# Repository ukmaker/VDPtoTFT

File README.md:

# VDPtoTFT
Converts the output from an old TMS9928A Video Display Processor to drive a small TFT panel using either an SPI or a parallel interface. For lovers of microcomputers from the 70s and 80s.

# Introduction
Once upon a time, when I were a lad, I had my very own Z80 based computer (Nascom 2) which I had built from a kit and then extended with cards of my own design. I always wanted a colour graphics card, and was most envious of computers which used the Texas Instruments TMS9918 family of chips. I never did get a graphics card, though I did build a two-channel DtoA converter and used that to drive my oscilloscope.

So, wind forward to todayish and I'm in the middle of a project to build a drum machine, when I discover a simple computer I'd cobbled together on a breadboard and which was now living in a box in the shed. Putting two and two together, I decided to see whether it would have been possible to build the drum machine using 70s technology. First thing to do was to decide on what would take the place of the TFT display. You can see where this is going, and how very deep that rabbit-hole is.

Right.

So, for anyone with an old computer using one of the TMS9928/29/128/129 chips, here is a project which will allow you to use it to drive a small, cheap TFT display. It won't work with the TMS9918 chips because it needs to sample the Y and R-Y outputs which don't exist on the TMS9918.

All it needs is an STM32G4 microcontroller. I used a Nucleo-G474RE board because I had one already.

# But Does It Work?
Yes, it does. I confess to being suprised that I was able to make it work. There is a little bit of flicker in a couple of the colours, due to noise in the sampling process, so I have a couple of improvements I'll be working on. 
- Tweak the on-board VREF to output a lower voltage (2.8V instead of 3.25) thus potentially increasing the ADC accuracy.
- Build a better custom PCB. The first version has some errors.

I may end up making a custom PCB including the TMS chip so there's an all-in-one solution for RC2014 folks. Let me know if you would like this.

# Pictures

My VDP board with the Nucleo bolted to the side

Yes, I'm cheating. Driving the VDP from an Arduino for now

Close up of an image on the SPI display

And a test-pattern on the parallel display

Here's a bit of test-gear I built to help. 
 - see my other project [VideoTrigger](https://github.com/ukmaker/VideoTrigger) for details

# Theory Of Operation

The following block diagram shows the essentials of how this works.

The output of the VDP's crystal oscillator is used to drive the clock input on the STM32G4. The STM32G4's PLL multiplies the VDP's 10.7MHz clock up by a factor of 16 to 171.2 MHz (thus ever so slightly overclocking the STM32, which is rated to 170MHz). This ensures that all processing happens synchronously to the signals being generated by the VDP. 

The VDP is capable of producing 16 different colours, and the generated signal comes from three outputs - Y, R-Y and B-Y. It turns out that sampling only Y and R-Y give us enough information to deduce the colour being generated, which is good as it reduces the amount of processing needed. These signals are fed to the STM's ADC1 and ADC2 which are operated in "dual-mode". This means that both inputs are sampled synchronously under the control of ADC1. The samples are place in a small circular buffer using DMA.

The ADCs are triggered by a timer which is in turn triggered by a comparator which samples the Y signal to determine when horizontal and vertical sync events happen (when the Y signal level drops below the black value). A trimpot is used to set this level correctly. Once a sync event is detected a chain of two timers is used to generate the sampling signals for the ADCs. The first timer (TIM4) starts the second timer (TIM1) after a delay calculated such that TIM1's first output pulse will happen just as the first pixel data is output by the VDP. This delay is approx 12 microseconds from the horizontal sync pulse.

The ADC's DMA channel is set to run in circular mode, with a buffer size of 512 half-words. The DMA unit will raise a transfer-half-complete interrupt after 256 transfers, which corresponds to one complete line of pixels. There are now approx 16us available for processing before the start of the next line. The interrupt service routine (ADCCallback()) uses this time to read the data from the buffer, map it from read values (samples are 6 bits per channel) to 16-bit RGB values and store them in the dma buffer, which holds an entire frame of samples. This repeats on the transfer-complete interrupt and so on until and entire frame has been sampled and mapped. 

If the sync signal stays low for more than one line-time (64 us), TIM3 will detect this as a vertical sync, and raise an interrupt. This is used by the state-machine running in the main() loop to initiate the DMA transfer from the RGB buffer to either the SPI unit or GPIO Port C if a parallel TFT is being used.

If SPI is being used, the transfer happens in 4 blocks because the maximum size for a single DMA transfer is 65536 transfers. One full frame holds 256 pixels * 192 lines * 2 bytes of data = 98,304 transfers (SPI config for my screen is in bytes). I.e. too many transfers for a single DMA session. The SPI interface is clocked at 42.8MHz, even though the datasheet for the chip used in my display (ILI9341) says the maximum SPI clock speed is 10MHz! Even so, there just is not enough time in one frame to sample and transfer all the data so instead the state machine runs a sample for a frame and then takes a frame to refresh the screen. This is visible as 30Hz flicker on the screen. I have ordered a TMS9129 to use in place of the TMS9128. The TMS9129 is the European version which has a 50Hz refresh rate rather than the 60Hz of the TMS9128. With this lower frame rate I think I'll be able to refresh the screen over SPI at a full 50Hz, thus eliminating the flicker.

If a parallel interface is being used the DMA controller can transfer the entire 49K RGB buffer in one go at 60Hz, so there is no flicker. The parallel interface runs at 10MHz.

# Building
This is a project built using the STM32CubeIDE and the STM32 HAL. If this offends you, feel free to fork my repo and rewrite it in whatever manner you choose.

For now, there is little to do to build this other than

- Install STM32CubeIDE if you haven't already got it
- Download this repo
- Open the project in the IDE and build it
- Tweak appropriate jumpers on your Nucleo (see below)
- Wire up a trimpot to set the sync level
- Connect the Nucleo to the display of your choice (see below)
- Connect the Nucleo to your VDP
- Plug everything in 
- Click Run in the IDE

Note that all the code etc is in the V1.0 directory. I had some small learning opportunities once I'd received my first set of PCBs, and the changes in the V2.0 folder are just for the schematic and layout.

The ConverterBoard directory contains a schematic for implementing this directly with an STM32G474.

The VDPtoSPI directory contains pseudo-schematics for how the blocks in the MCU are used.

## Nucleo Tweaking
Because I needed to use quite a few pins in non-standard ways (for a Nucleo), I needed to remove quite a few jumpers. I'm not sure I remember them all now, but here goes:

### Using the clock from the VDP to drive HSE on PF0.
```
SB28 ON (Connect OSCIN to PF0 header pin)
SB24, SB25, SB26, 27 OFF 
```
### Connect PC14 and PC15 to header pins
```
SB29, SB32 ON
```

### The Sync Trimpot
The sync signal is derived by configuring Comparator 1 and feeding the positive input with the Y signal and the negative input with a constant voltage from a trimpot to set the threshold. Connecct a trimmer of e.g. 10K to 3V3 and GND, with the wiper going to PB1. You should also add a decoupling capacitor of e.g. 100n from PB1 to ground.

Once the board is up and running and you are feeding it a signal from your VDP, adjust the trimpot to obtain a stable display. This can bbe made easier with a two-channel scope attached to Y and PB1 so you can position the voltage on PB1 in the middle of the sync tips.

If you have trouble getting your scope to sync to the VDP signal you might want to look at my other project which is a tool to get a clean trigger off any chosen line on the display. https://github.com/ukmaker/VideoTrigger

## Connecting Your Display
The code is capable of driving displays using either an SPI or parallel interface. 

Configuration is in the file

`V1.0/STM32CubeIDE/VDPDMA/Core/Inc/configuration.h`

By default the code expects to use an SPI interface using SPI2
```
  CS - PB9
  DC - PB8
  RS - PD2
  MOSI - PA11
  SCK - PF1
```
If you uncomment the line
`#define PAR_TFT`
then the code will expect a parallel display
```
D0 - D15 -> PC0 - PC15
CS - PB11
RS - PB12
RD - PB14
RESET - PB15
```

# Making the PCB
Don't use the V1.0 board - there are some annoying errors.

Also, I hope you're better at soldering surface-mount than I am. My first attempt is best described using words like "embarrassment", "cringe" and "pillock". Watch out for those STM chips. Sometimes they have two little circles on the package. Make sure you know which one means Pin 1 Is Here. Then make sure again.

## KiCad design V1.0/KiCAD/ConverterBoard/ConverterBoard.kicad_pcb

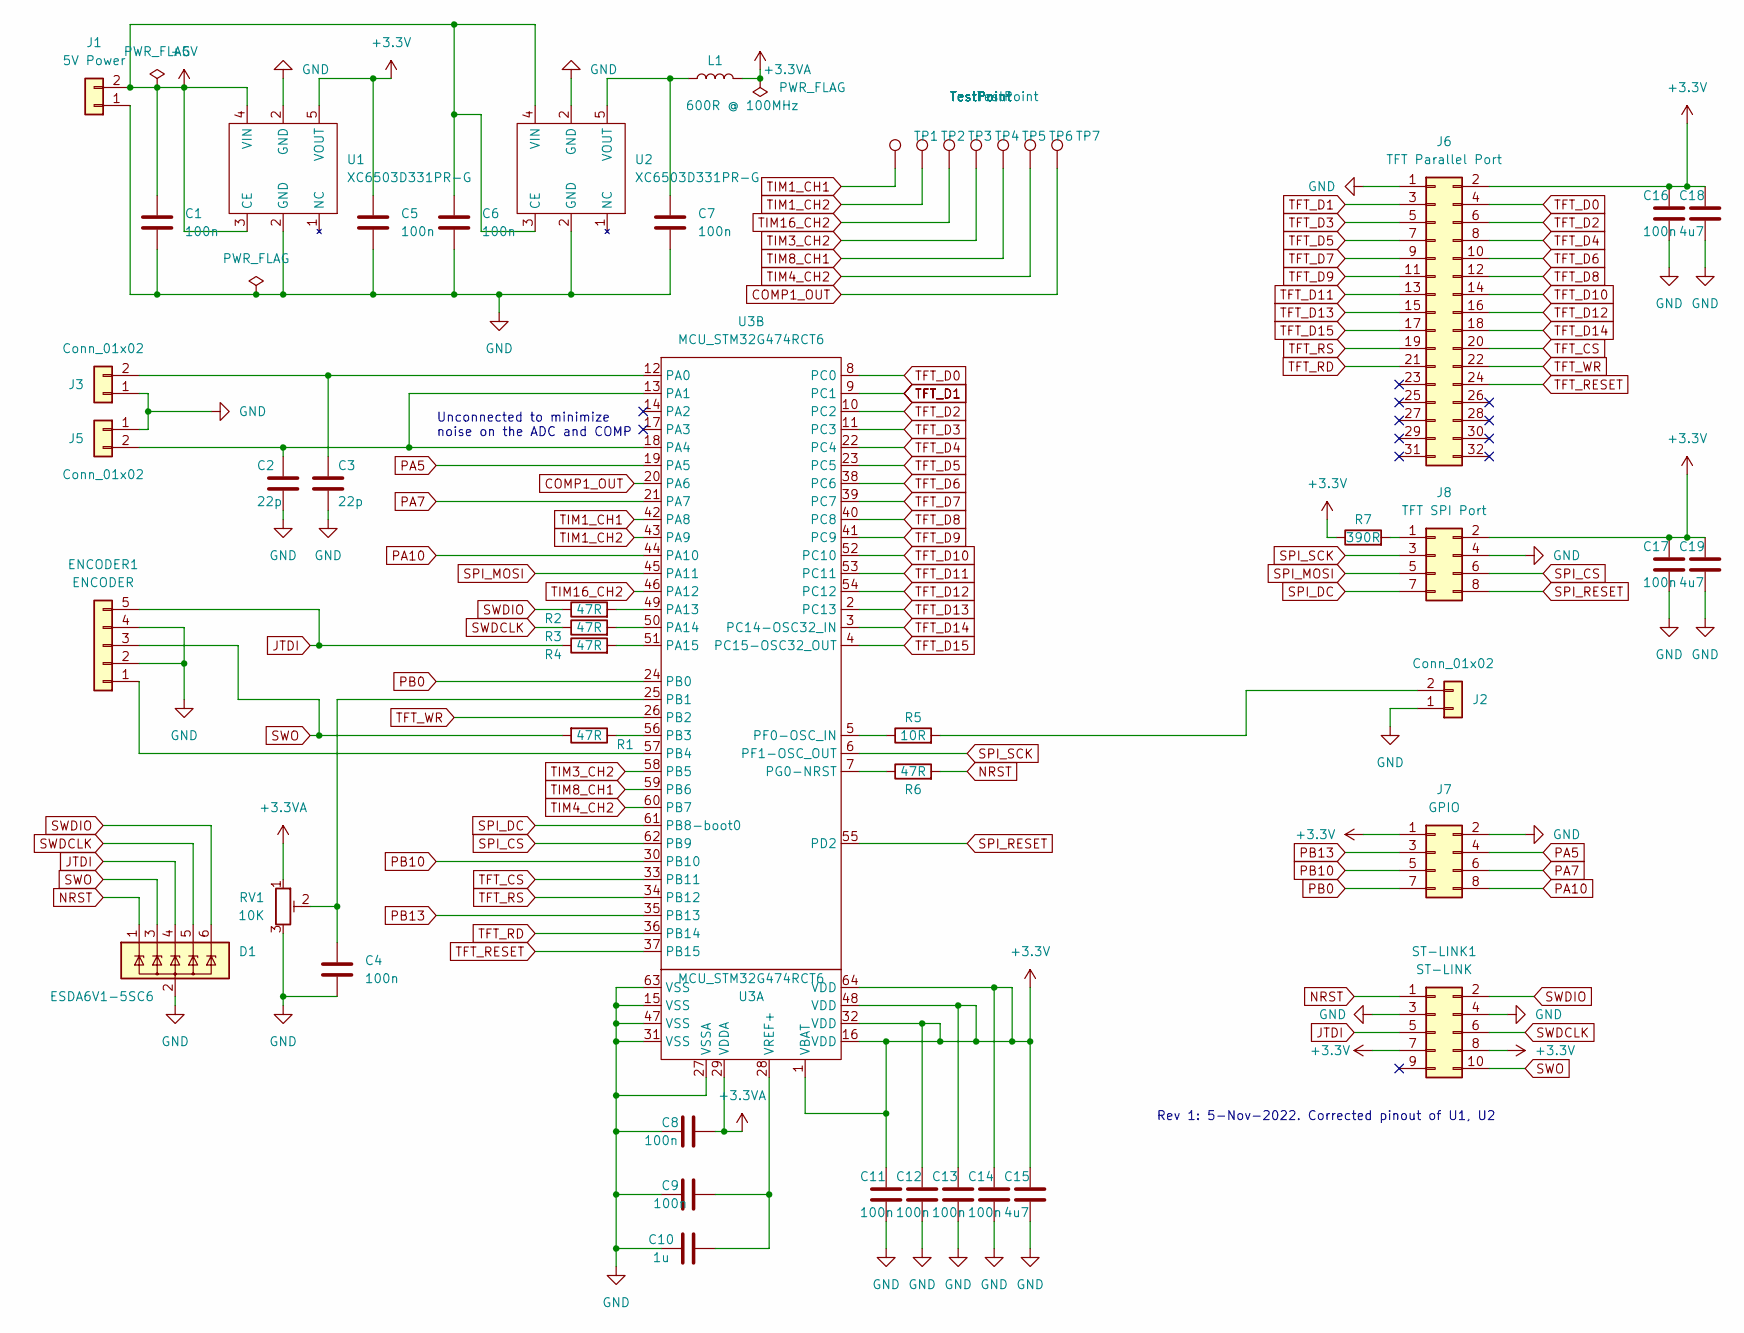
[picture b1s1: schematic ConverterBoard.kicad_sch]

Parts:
C1, C4, C5, C6, C7, C8, C9, C11, C12, C13, C14, C16, C17: 100n; C_0805_2012Metric
C2, C3: 22p; C_0805_2012Metric
C10: 1u; C_0805_2012Metric
C15, C18, C19: 4u7; C_0805_2012Metric
D1: ESDA6V1-5SC6; SOT-23-6
ENCODER1: ENCODER; PinHeader_1x05_P2.54mm_Vertical
J1: 5V Power; TerminalBlock_bornier-2_P5.08mm
J2, J3, J5: Conn_01x02; PinHeader_1x02_P2.54mm_Vertical
J6: TFT Parallel Port; PinHeader_2x16_P2.54mm_Vertical
J7: GPIO; PinHeader_2x04_P2.54mm_Vertical
J8: TFT SPI Port; PinHeader_2x04_P2.54mm_Vertical
L1: 600R @ 100MHz; L_0805_2012Metric_Pad1.15x1.40mm_HandSolder
R1, R2, R3, R4, R6: 47R; R_0805_2012Metric_Pad1.20x1.40mm_HandSolder
R5: 10R; R_0805_2012Metric_Pad1.20x1.40mm_HandSolder
R7: 390R; R_0805_2012Metric_Pad1.20x1.40mm_HandSolder
RV1: 10K; Potentiometer_Bourns_3005_Horizontal
ST-LINK1: ST-LINK; PinHeader_2x05_P2.54mm_Vertical
TP1, TP2, TP3, TP4, TP5, TP6, TP7: TestPoint; TestPoint_THTPad_1.5x1.5mm_Drill0.7mm
U1, U2: XC6503D331PR-G; SOT-89-5_Handsoldering
U3: MCU_STM32G474RCT6; LQFP-64_10x10mm_P0.5mm

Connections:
+3.3V: C5.1, C11.1, C12.1, C13.1, C14.1, C15.1, C16.1, C17.1, C18.1, C19.1, J6.2, J7.1, J8.2, R7.1, ST-LINK1.7, ST-LINK1.8, U1.5 (VOUT), U3.1 (VBAT), U3.16 (VDD), U3.32 (VDD), U3.48 (VDD), U3.64 (VDD)
+3.3VA: C8.2, L1.2, RV1.1, U3.29 (VDDA)
+5V: C1.1, C6.1, J1.2, U1.3 (CE), U1.4 (VIN), U2.3 (CE), U2.4 (VIN)
COMP1_OUT: TP7.1, U3.20 (PA6)
GND: C1.2, C2.2, C3.2, C4.2, C5.2, C6.2, C7.2, C8.1, C9.1, C10.1, C11.2, C12.2, C13.2, C14.2, C15.2, C16.2, C17.2, C18.2, C19.2, D1.2 (GND), ENCODER1.2, ENCODER1.4, J1.1, J2.1, J3.1, J5.1, J6.1, J7.2, J8.4, RV1.3, ST-LINK1.3, ST-LINK1.4, U1.2 (GND), U2.2 (GND), U3.15 (VSS), U3.27 (VSSA), U3.31 (VSS), U3.47 (VSS), U3.63 (VSS)
JTDI: D1.4 (IO3), ENCODER1.5, R4.1, ST-LINK1.5
NRST: D1.1 (IO1), R6.2, ST-LINK1.1
unnamed: C2.1, J5.2, U3.13 (PA1), U3.18 (PA4)
unnamed: C3.1, J3.2, U3.12 (PA0)
unnamed: C4.1, RV1.2, U3.25 (PB1)
unnamed: C9.2, C10.2, U3.28 (VREF+)
unnamed: ENCODER1.1, U3.57 (PB4)
unnamed: J2.2, R5.2
unnamed: J8.1, R7.2
unnamed: R1.1, U3.56 (PB3)
unnamed: R2.2, U3.49 (PA13)
unnamed: R3.2, U3.50 (PA14)
unnamed: R4.2, U3.51 (PA15)
unnamed: R5.1, U3.5 (PF0-OSC_IN)
unnamed: R6.1, U3.7 (PG0-NRST)
unnamed: C7.1, L1.1, U2.5 (VOUT)
PA5: J7.4, U3.19 (PA5)
PA7: J7.6, U3.21 (PA7)
PA10: J7.8, U3.44 (PA10)
PB0: J7.7, U3.24 (PB0)
PB10: J7.5, U3.30 (PB10)
PB13: J7.3, U3.35 (PB13)
SPI_CS: J8.6, U3.62 (PB9)
SPI_DC: J8.7, U3.61 (PB8-boot0)
SPI_MOSI: J8.5, U3.45 (PA11)
SPI_RESET: J8.8, U3.55 (PD2)
SPI_SCK: J8.3, U3.6 (PF1-OSC_OUT)
SWDCLK: D1.5 (IO4), R3.1, ST-LINK1.6
SWDIO: D1.6 (IO5), R2.1, ST-LINK1.2
SWO: D1.3 (IO2), ENCODER1.3, R1.2, ST-LINK1.10
TFT_CS: J6.20, U3.33 (PB11)
TFT_D0: J6.4, U3.8 (PC0)
TFT_D1: J6.3, U3.9 (PC1)
TFT_D2: J6.6, U3.10 (PC2)
TFT_D3: J6.5, U3.11 (PC3)
TFT_D4: J6.8, U3.22 (PC4)
TFT_D5: J6.7, U3.23 (PC5)
TFT_D6: J6.10, U3.38 (PC6)
TFT_D7: J6.9, U3.39 (PC7)
TFT_D8: J6.12, U3.40 (PC8)
TFT_D9: J6.11, U3.41 (PC9)
TFT_D10: J6.14, U3.52 (PC10)
TFT_D11: J6.13, U3.53 (PC11)
TFT_D12: J6.16, U3.54 (PC12)
TFT_D13: J6.15, U3.2 (PC13)
TFT_D14: J6.18, U3.3 (PC14-OSC32_IN)
TFT_D15: J6.17, U3.4 (PC15-OSC32_OUT)
TFT_RD: J6.21, U3.36 (PB14)
TFT_RESET: J6.24, U3.37 (PB15)
TFT_RS: J6.19, U3.34 (PB12)
TFT_WR: J6.22, U3.26 (PB2)
TIM1_CH1: TP1.1, U3.42 (PA8)
TIM1_CH2: TP2.1, U3.43 (PA9)
TIM3_CH2: TP4.1, U3.58 (PB5)
TIM4_CH2: TP6.1, U3.60 (PB7)
TIM8_CH1: TP5.1, U3.59 (PB6)
TIM16_CH2: TP3.1, U3.46 (PA12)

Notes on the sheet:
Rev 1: 5-Nov-2022. Corrected pinout of U1, U2
Unconnected to minimize noise on the ADC and COMP

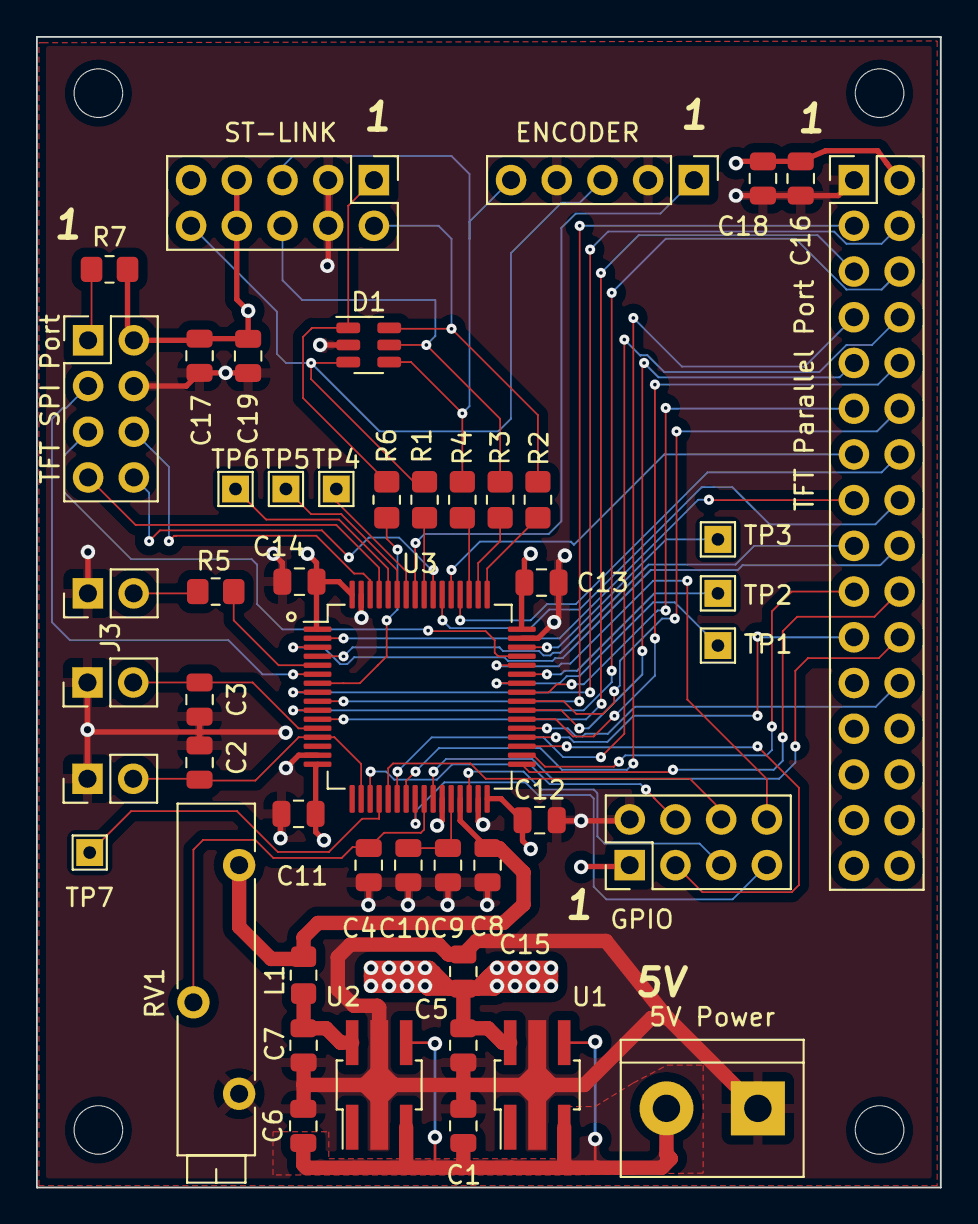
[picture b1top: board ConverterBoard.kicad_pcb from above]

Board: 4 copper layers, 50.2 x 63.9 mm, 48 parts (0 on the bottom side), 62 nets.

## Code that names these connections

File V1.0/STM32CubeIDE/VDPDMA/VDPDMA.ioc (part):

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Mcu.Name=STM32G474R(B-C-E)Tx
Mcu.Package=LQFP64
Mcu.UserName=STM32G474RETx
PA0.Mode=IN1-Single-Ended
PA0.Signal=ADC1_IN1
PA1.Mode=IN2-Single-Ended
PA1.Signal=ADC2_IN2
PA11.GPIOParameters=GPIO_Speed
PA11.GPIO_Speed=GPIO_SPEED_FREQ_HIGH
PA11.Mode=Simplex_Bidirectional_Master
PA11.Signal=SPI2_MOSI
PA12.Signal=S_TIM16_CH1
PA15.GPIOParameters=GPIO_PuPd
PA15.GPIO_PuPd=GPIO_PULLUP
PA15.Signal=S_TIM2_CH1
PA4.Mode=INM
PA4.Signal=COMP1_INM
PA5.GPIOParameters=GPIO_Speed,PinState,GPIO_PuPd,GPIO_ModeDefaultOutputPP
PA5.GPIO_ModeDefaultOutputPP=GPIO_MODE_OUTPUT_PP
PA5.GPIO_PuPd=GPIO_NOPULL
PA5.GPIO_Speed=GPIO_SPEED_FREQ_MEDIUM
PA5.PinState=GPIO_PIN_RESET
PA5.Signal=GPIO_Output
PA6.Signal=COMP1_OUT
PA8.Signal=S_TIM1_CH1
PA9.Signal=S_TIM1_CH2
PB1.Mode=INP
PB1.Signal=COMP1_INP
PB11.GPIOParameters=GPIO_Speed,PinState,GPIO_PuPd,GPIO_ModeDefaultOutputPP
PB11.GPIO_ModeDefaultOutputPP=GPIO_MODE_OUTPUT_PP
PB11.GPIO_PuPd=GPIO_NOPULL
PB11.GPIO_Speed=GPIO_SPEED_FREQ_LOW
PB11.PinState=GPIO_PIN_SET
PB11.Signal=GPIO_Output
PB12.GPIOParameters=GPIO_Speed,PinState,GPIO_PuPd,GPIO_ModeDefaultOutputPP
PB12.GPIO_ModeDefaultOutputPP=GPIO_MODE_OUTPUT_PP
PB12.GPIO_PuPd=GPIO_NOPULL
PB12.GPIO_Speed=GPIO_SPEED_FREQ_LOW
PB12.PinState=GPIO_PIN_SET
PB12.Signal=GPIO_Output
PB14.GPIOParameters=GPIO_Speed,PinState,GPIO_PuPd,GPIO_ModeDefaultOutputPP
PB14.GPIO_ModeDefaultOutputPP=GPIO_MODE_OUTPUT_PP
PB14.GPIO_PuPd=GPIO_NOPULL
PB14.GPIO_Speed=GPIO_SPEED_FREQ_LOW
PB14.PinState=GPIO_PIN_SET
PB14.Signal=GPIO_Output
PB15.GPIOParameters=GPIO_Speed,PinState,GPIO_PuPd,GPIO_ModeDefaultOutputPP
PB15.GPIO_ModeDefaultOutputPP=GPIO_MODE_OUTPUT_PP
PB15.GPIO_PuPd=GPIO_NOPULL
PB15.GPIO_Speed=GPIO_SPEED_FREQ_LOW
PB15.PinState=GPIO_PIN_SET
PB15.Signal=GPIO_Output
PB2.GPIOParameters=GPIO_ModeDefaultPP,GPIO_Speed,GPIO_PuPd
PB2.GPIO_ModeDefaultPP=GPIO_MODE_AF_PP
PB2.GPIO_PuPd=GPIO_NOPULL
PB2.GPIO_Speed=GPIO_SPEED_FREQ_HIGH
PB2.Mode=PWM Generation1 CH1
PB2.Signal=TIM20_CH1
PB3.GPIOParameters=GPIO_PuPd
PB3.GPIO_PuPd=GPIO_PULLUP
PB3.Signal=S_TIM2_CH2
PB4.GPIOParameters=GPIO_PuPd
PB4.GPIO_PuPd=GPIO_PULLUP
PB4.Signal=GPIO_Input
PB5.Signal=S_TIM3_CH2
PB6.Signal=S_TIM8_CH1
PB7.Signal=S_TIM4_CH2
PB8-BOOT0.GPIOParameters=GPIO_Speed
PB8-BOOT0.GPIO_Speed=GPIO_SPEED_FREQ_VERY_HIGH
PB8-BOOT0.Signal=GPIO_Output
PB9.GPIOParameters=GPIO_Speed,PinState,GPIO_FM9
PB9.GPIO_FM9=SYSCFG_FASTMODEPLUS_PB9
PB9.GPIO_Speed=GPIO_SPEED_FREQ_VERY_HIGH
PB9.PinState=GPIO_PIN_SET
PB9.Signal=GPIO_Output
PC0.GPIOParameters=GPIO_Speed,PinState,GPIO_PuPd,GPIO_ModeDefaultOutputPP
PC0.GPIO_ModeDefaultOutputPP=GPIO_MODE_OUTPUT_PP
PC0.GPIO_PuPd=GPIO_NOPULL
PC0.GPIO_Speed=GPIO_SPEED_FREQ_LOW
PC0.PinState=GPIO_PIN_RESET
PC0.Signal=GPIO_Output
PC1.GPIOParameters=GPIO_Speed,PinState,GPIO_PuPd,GPIO_ModeDefaultOutputPP
PC1.GPIO_ModeDefaultOutputPP=GPIO_MODE_OUTPUT_PP
PC1.GPIO_PuPd=GPIO_NOPULL
PC1.GPIO_Speed=GPIO_SPEED_FREQ_LOW
PC1.PinState=GPIO_PIN_RESET
PC1.Signal=GPIO_Output
PC10.GPIOParameters=GPIO_Speed,PinState,GPIO_PuPd,GPIO_ModeDefaultOutputPP
PC10.GPIO_ModeDefaultOutputPP=GPIO_MODE_OUTPUT_PP
PC10.GPIO_PuPd=GPIO_NOPULL
PC10.GPIO_Speed=GPIO_SPEED_FREQ_LOW
PC10.PinState=GPIO_PIN_RESET
PC10.Signal=GPIO_Output
PC11.GPIOParameters=GPIO_Speed,PinState,GPIO_PuPd,GPIO_ModeDefaultOutputPP
PC11.GPIO_ModeDefaultOutputPP=GPIO_MODE_OUTPUT_PP
PC11.GPIO_PuPd=GPIO_NOPULL
PC11.GPIO_Speed=GPIO_SPEED_FREQ_LOW
PC11.PinState=GPIO_PIN_RESET
PC11.Signal=GPIO_Output
PC12.GPIOParameters=GPIO_Speed,PinState,GPIO_PuPd,GPIO_ModeDefaultOutputPP
PC12.GPIO_ModeDefaultOutputPP=GPIO_MODE_OUTPUT_PP
PC12.GPIO_PuPd=GPIO_NOPULL
PC12.GPIO_Speed=GPIO_SPEED_FREQ_LOW
PC12.PinState=GPIO_PIN_RESET
PC12.Signal=GPIO_Output
PC13.GPIOParameters=GPIO_Speed,PinState,GPIO_PuPd,GPIO_ModeDefaultOutputPP
PC13.GPIO_ModeDefaultOutputPP=GPIO_MODE_OUTPUT_PP
PC13.GPIO_PuPd=GPIO_NOPULL
PC13.GPIO_Speed=GPIO_SPEED_FREQ_LOW
PC13.PinState=GPIO_PIN_RESET
PC13.Signal=GPIO_Output
PC14-OSC32_IN.Signal=GPIO_Output
PC15-OSC32_OUT.GPIOParameters=GPIO_Speed,PinState,GPIO_PuPd,GPIO_ModeDefaultOutputPP
PC15-OSC32_OUT.GPIO_ModeDefaultOutputPP=GPIO_MODE_OUTPUT_PP
PC15-OSC32_OUT.GPIO_PuPd=GPIO_NOPULL
PC15-OSC32_OUT.GPIO_Speed=GPIO_SPEED_FREQ_LOW
PC15-OSC32_OUT.PinState=GPIO_PIN_RESET
PC15-OSC32_OUT.Signal=GPIO_Output
PC2.GPIOParameters=GPIO_Speed,PinState,GPIO_PuPd,GPIO_ModeDefaultOutputPP
PC2.GPIO_ModeDefaultOutputPP=GPIO_MODE_OUTPUT_PP
PC2.GPIO_PuPd=GPIO_NOPULL
PC2.GPIO_Speed=GPIO_SPEED_FREQ_LOW
PC2.PinState=GPIO_PIN_RESET
PC2.Signal=GPIO_Output
PC3.GPIOParameters=GPIO_Speed,PinState,GPIO_PuPd,GPIO_ModeDefaultOutputPP
PC3.GPIO_ModeDefaultOutputPP=GPIO_MODE_OUTPUT_PP
PC3.GPIO_PuPd=GPIO_NOPULL
PC3.GPIO_Speed=GPIO_SPEED_FREQ_LOW
PC3.PinState=GPIO_PIN_RESET
PC3.Signal=GPIO_Output
PC4.GPIOParameters=GPIO_Speed,PinState,GPIO_PuPd,GPIO_ModeDefaultOutputPP
PC4.GPIO_ModeDefaultOutputPP=GPIO_MODE_OUTPUT_PP
PC4.GPIO_PuPd=GPIO_NOPULL
PC4.GPIO_Speed=GPIO_SPEED_FREQ_LOW
PC4.PinState=GPIO_PIN_RESET
PC4.Signal=GPIO_Output
PC5.GPIOParameters=GPIO_Speed,PinState,GPIO_PuPd,GPIO_ModeDefaultOutputPP
PC5.GPIO_ModeDefaultOutputPP=GPIO_MODE_OUTPUT_PP
PC5.GPIO_PuPd=GPIO_NOPULL
PC5.GPIO_Speed=GPIO_SPEED_FREQ_LOW
PC5.PinState=GPIO_PIN_RESET
PC5.Signal=GPIO_Output
PC6.GPIOParameters=GPIO_Speed,PinState,GPIO_PuPd,GPIO_ModeDefaultOutputPP
PC6.GPIO_ModeDefaultOutputPP=GPIO_MODE_OUTPUT_PP
PC6.GPIO_PuPd=GPIO_NOPULL
PC6.GPIO_Speed=GPIO_SPEED_FREQ_LOW
PC6.PinState=GPIO_PIN_RESET
PC6.Signal=GPIO_Output
PC7.GPIOParameters=GPIO_Speed,PinState,GPIO_PuPd,GPIO_ModeDefaultOutputPP
PC7.GPIO_ModeDefaultOutputPP=GPIO_MODE_OUTPUT_PP
PC7.GPIO_PuPd=GPIO_NOPULL
PC7.GPIO_Speed=GPIO_SPEED_FREQ_LOW
PC7.PinState=GPIO_PIN_RESET
PC7.Signal=GPIO_Output
PC8.GPIOParameters=GPIO_Speed,PinState,GPIO_PuPd,GPIO_ModeDefaultOutputPP
PC8.GPIO_ModeDefaultOutputPP=GPIO_MODE_OUTPUT_PP
PC8.GPIO_PuPd=GPIO_NOPULL
PC8.GPIO_Speed=GPIO_SPEED_FREQ_LOW
PC8.PinState=GPIO_PIN_RESET
PC8.Signal=GPIO_Output
PC9.GPIOParameters=GPIO_Speed,PinState,GPIO_PuPd,GPIO_ModeDefaultOutputPP
PC9.GPIO_ModeDefaultOutputPP=GPIO_MODE_OUTPUT_PP
PC9.GPIO_PuPd=GPIO_NOPULL
PC9.GPIO_Speed=GPIO_SPEED_FREQ_LOW
PC9.PinState=GPIO_PIN_RESET
PC9.Signal=GPIO_Output
PD2.GPIOParameters=PinState
PD2.PinState=GPIO_PIN_SET
PD2.Signal=GPIO_Output
PF0-OSC_IN.Mode=HSE-External-Clock-Source
PF0-OSC_IN.Signal=RCC_OSC_IN
PF1-OSC_OUT.GPIOParameters=GPIO_Speed
PF1-OSC_OUT.GPIO_Speed=GPIO_SPEED_FREQ_HIGH
PF1-OSC_OUT.Mode=Simplex_Bidirectional_Master
PF1-OSC_OUT.Signal=SPI2_SCK
RCC.HSE_VALUE=7500000
RCC.SYSCLKFreq_VALUE=120000000
RCC.SYSCLKSource=RCC_SYSCLKSOURCE_PLLCLK
board=custom

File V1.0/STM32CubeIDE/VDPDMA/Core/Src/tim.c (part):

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
    __HAL_RCC_GPIOA_CLK_ENABLE();
    /**TIM1 GPIO Configuration
    PA9     ------> TIM1_CH2
    */
    GPIO_InitStruct.Pin = GPIO_PIN_9;
    GPIO_InitStruct.Mode = GPIO_MODE_AF_PP;
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
    __HAL_RCC_GPIOB_CLK_ENABLE();
    /**TIM3 GPIO Configuration
    PB5     ------> TIM3_CH2
    */
    GPIO_InitStruct.Pin = GPIO_PIN_5;
    GPIO_InitStruct.Mode = GPIO_MODE_AF_PP;
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
    __HAL_RCC_GPIOB_CLK_ENABLE();
    /**TIM4 GPIO Configuration
    PB7     ------> TIM4_CH2
    */
    GPIO_InitStruct.Pin = GPIO_PIN_7;
    GPIO_InitStruct.Mode = GPIO_MODE_AF_PP;
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    __HAL_RCC_GPIOA_CLK_ENABLE();
    __HAL_RCC_GPIOB_CLK_ENABLE();
    /**TIM2 GPIO Configuration
    PA15     ------> TIM2_CH1
    PB3     ------> TIM2_CH2
    */
    GPIO_InitStruct.Pin = GPIO_PIN_15;
    GPIO_InitStruct.Mode = GPIO_MODE_AF_PP;
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  /* USER CODE END TIM1_MspPostInit 0 */
    __HAL_RCC_GPIOA_CLK_ENABLE();
    /**TIM1 GPIO Configuration
    PA8     ------> TIM1_CH1
    */
    GPIO_InitStruct.Pin = GPIO_PIN_8;
    GPIO_InitStruct.Mode = GPIO_MODE_AF_PP;
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
    __HAL_RCC_GPIOB_CLK_ENABLE();
    /**TIM8 GPIO Configuration
    PB6     ------> TIM8_CH1
    */
    GPIO_InitStruct.Pin = GPIO_PIN_6;
    GPIO_InitStruct.Mode = GPIO_MODE_AF_PP;
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
    __HAL_RCC_GPIOA_CLK_ENABLE();
    /**TIM16 GPIO Configuration
    PA12     ------> TIM16_CH1
    */
    GPIO_InitStruct.Pin = GPIO_PIN_12;
    GPIO_InitStruct.Mode = GPIO_MODE_AF_PP;
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
    __HAL_RCC_GPIOB_CLK_ENABLE();
    /**TIM20 GPIO Configuration
    PB2     ------> TIM20_CH1
    */
    GPIO_InitStruct.Pin = GPIO_PIN_2;
    GPIO_InitStruct.Mode = GPIO_MODE_AF_PP;
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    __HAL_RCC_TIM1_CLK_DISABLE();

    /**TIM1 GPIO Configuration
    PA8     ------> TIM1_CH1
    PA9     ------> TIM1_CH2
    */
    HAL_GPIO_DeInit(GPIOA, GPIO_PIN_8|GPIO_PIN_9);

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    __HAL_RCC_TIM3_CLK_DISABLE();

    /**TIM3 GPIO Configuration
    PB5     ------> TIM3_CH2
    */
    HAL_GPIO_DeInit(GPIOB, GPIO_PIN_5);

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    __HAL_RCC_TIM4_CLK_DISABLE();

    /**TIM4 GPIO Configuration
    PB7     ------> TIM4_CH2
    */
    HAL_GPIO_DeInit(GPIOB, GPIO_PIN_7);

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    __HAL_RCC_TIM2_CLK_DISABLE();

    /**TIM2 GPIO Configuration
    PA15     ------> TIM2_CH1
    PB3     ------> TIM2_CH2
    */
    HAL_GPIO_DeInit(GPIOA, GPIO_PIN_15);

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
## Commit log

2022-09-11 Initial import
2022-09-11 Ignore ZIP files in git
2022-09-11 Add images
2022-09-11 Documentation
2022-09-12 Sync RGB_BUF_CHUNKS with no of TIM8 repititions
2022-09-12 Move SPI to SPI2 to free up TIM2 for reading an encoder
2022-09-14 Started to add support for settings
2023-01-07 README update and PCB outputs
2023-01-07 README
2023-01-07 More README updates

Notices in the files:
V1.0/STM32CubeIDE/VDPDMA/Core/Src/tim.c:
Copyright (c) 2022 STMicroelectronics.
All rights reserved.
This software is licensed under terms that can be found in the LICENSE file
